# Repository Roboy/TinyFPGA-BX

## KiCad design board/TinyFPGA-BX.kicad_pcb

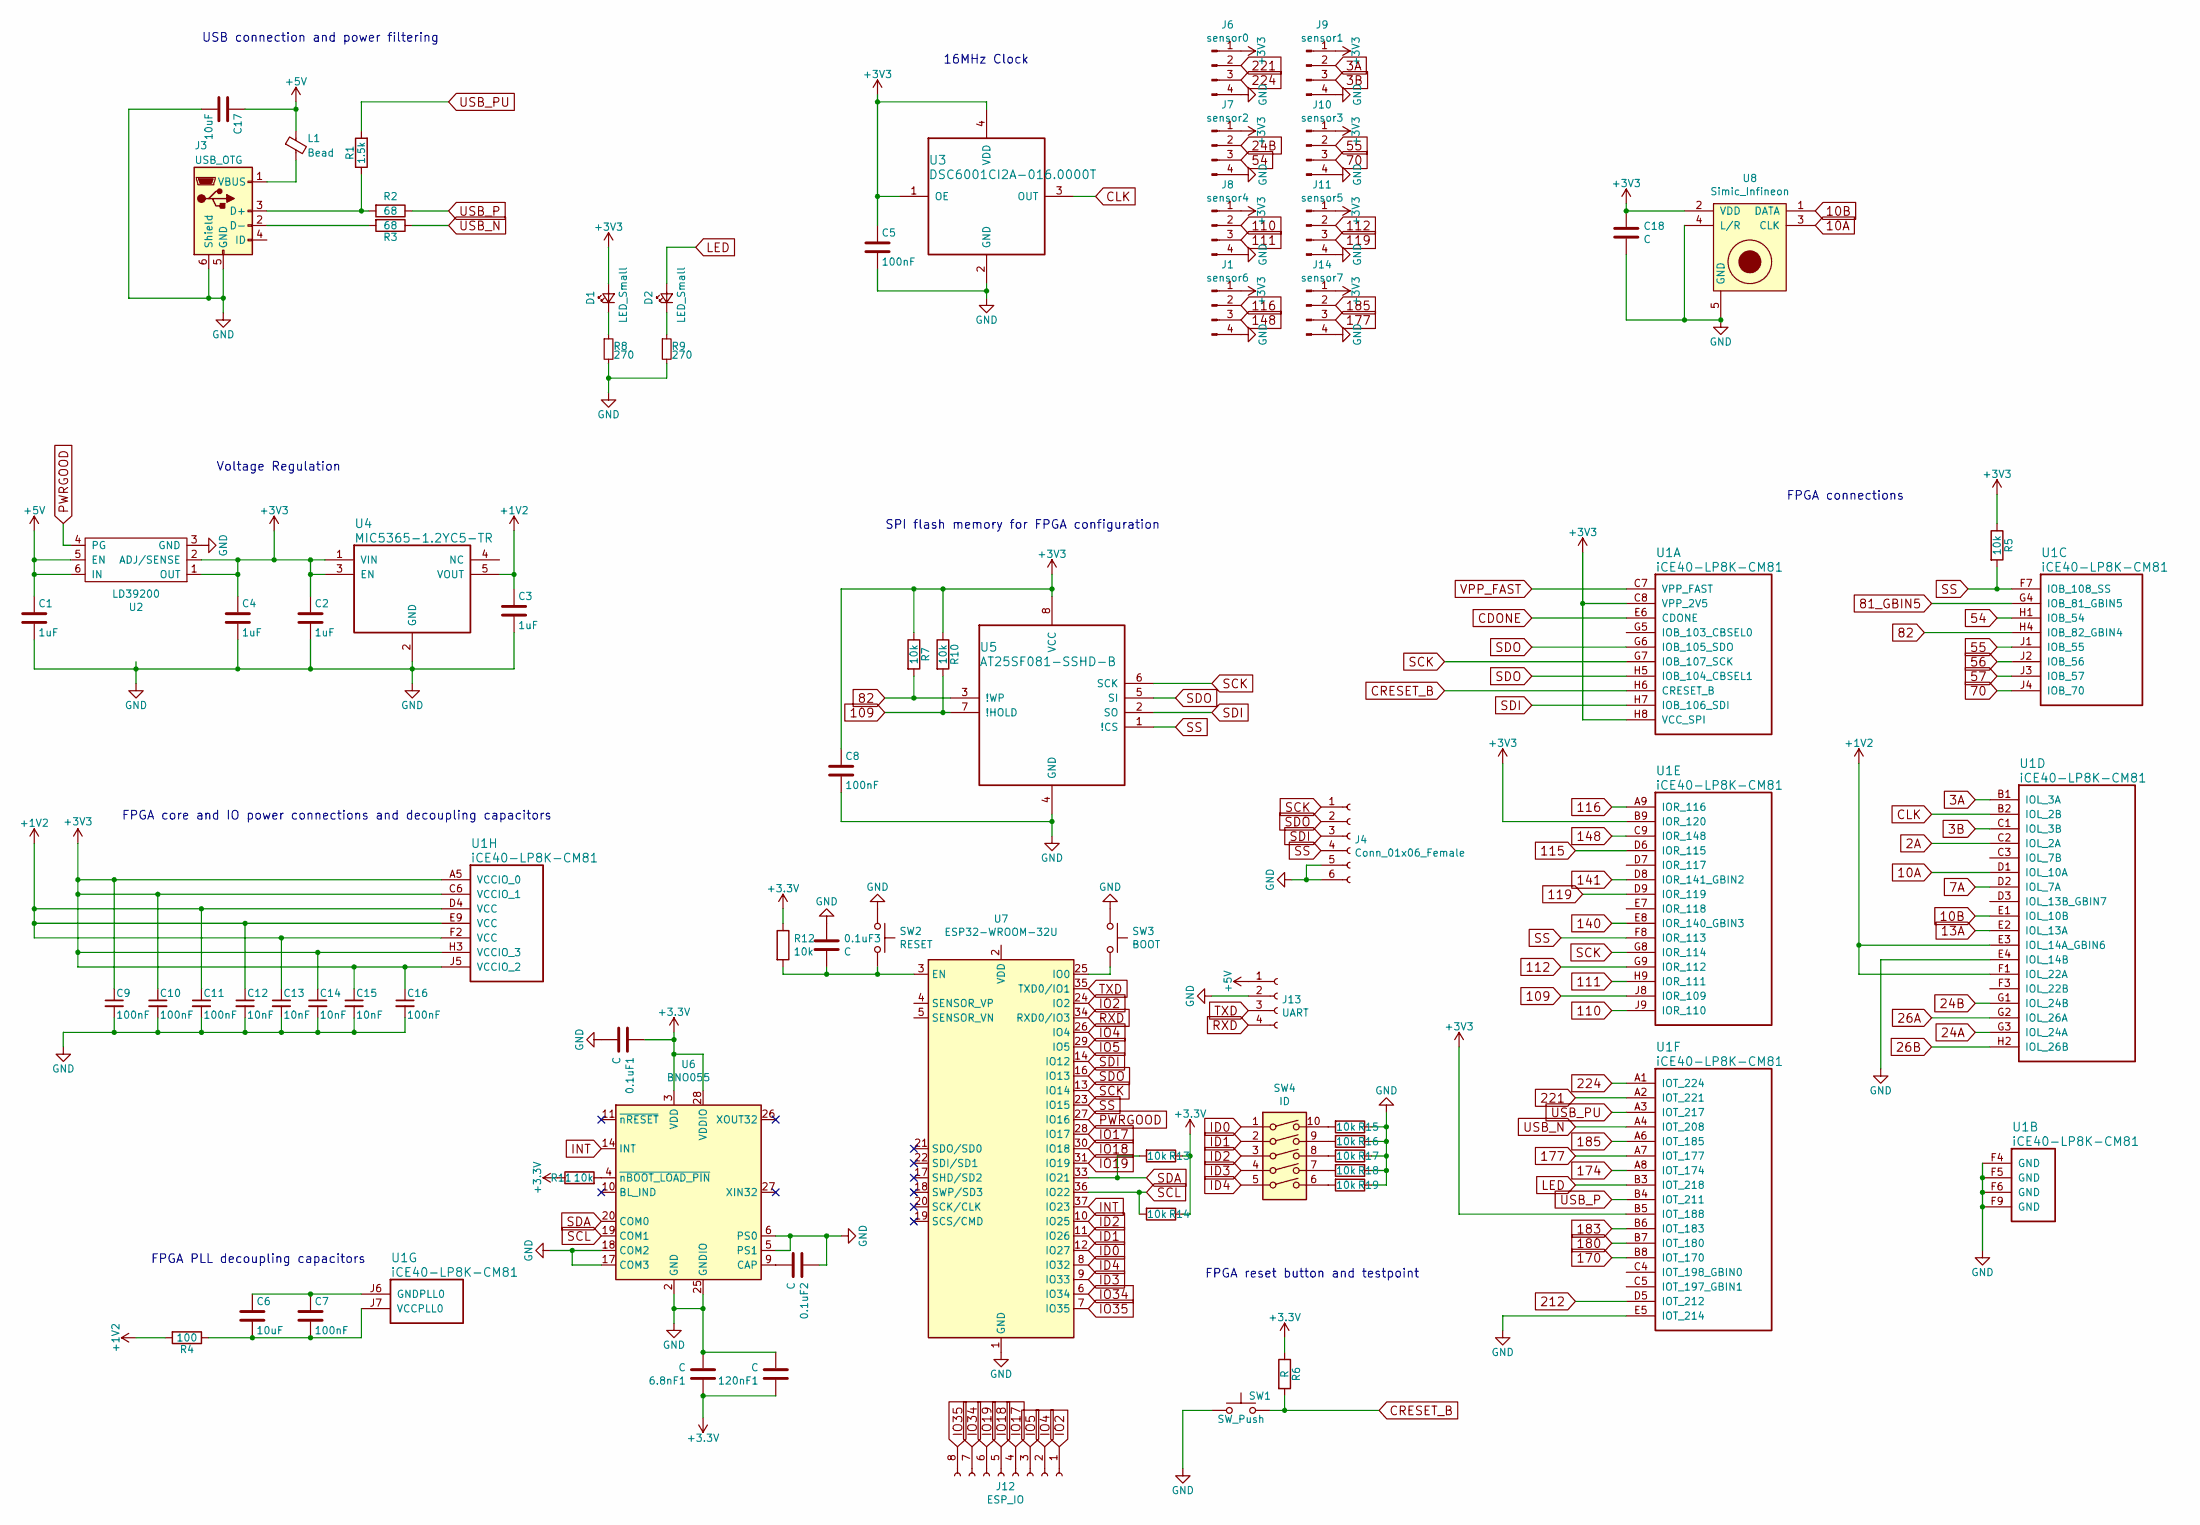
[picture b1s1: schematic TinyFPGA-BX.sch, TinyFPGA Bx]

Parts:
0.1uF1, 0.1uF2, 0.1uF3, 6.8nF1, 120nF1: C; C_0402_1005Metric
C1, C2, C3, C4: 1uF; C_0402_NoSilk
C5, C7, C8, C9, C10, C11, C16: 100nF; C_0402_NoSilk
C6, C17: 10uF; C_0603
C12, C13, C14, C15: 10nF; C_0402_NoSilk
C18: C; C_01005_0402Metric
D1, D2: LED_Small; LED_0603
J1: sensor6; TE-Connectivity_Micro-Match_connector_02x02_Pitch_1.27mm
J3: USB_OTG; USB_Micro-B_Molex_47346-0001
J4: Conn_01x06_Female; TE-Connectivity_Micro-Match_connector_02x03_Pitch_1.27mm
J6: sensor0; TE-Connectivity_Micro-Match_connector_02x02_Pitch_1.27mm
J7: sensor2; TE-Connectivity_Micro-Match_connector_02x02_Pitch_1.27mm
J8: sensor4; TE-Connectivity_Micro-Match_connector_02x02_Pitch_1.27mm
J9: sensor1; TE-Connectivity_Micro-Match_connector_02x02_Pitch_1.27mm
J10: sensor3; TE-Connectivity_Micro-Match_connector_02x02_Pitch_1.27mm
J11: sensor5; TE-Connectivity_Micro-Match_connector_02x02_Pitch_1.27mm
J12: ESP_IO; PinHeader_1x08_P2.54mm_Vertical
J13: UART; PinHeader_1x04_P2.54mm_Vertical
J14: sensor7; TE-Connectivity_Micro-Match_connector_02x02_Pitch_1.27mm
L1: Bead; L_0603
R1: 1.5k; R_0402_NoSilk
R2, R3: 68; R_0402_NoSilk
R4: 100; R_0402_NoSilk
R5, R7, R10: 10k; R_0402_NoSilk
R6: R; R_0402
R8, R9: 270; R_0402_NoSilk
R11, R12, R13, R14, R15, R16, R17, R18, R19: 10k; R_0402_1005Metric
SW1: SW_Push; PTS_810_SMT_Switch
SW2: RESET; SW_SPST_KXT3
SW3: BOOT; SW_SPST_KXT3
SW4: ID; SW_DIP_SPSTx05_Slide_6.7x14.26mm_W6.73mm_P2.54mm_LowProfile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
U1: iCE40-LP8K-CM81; CM81
U2: LD39200; DFN-6-1EP_3x3mm_P0.95mm_EP1.7x2.6mm
U3: DSC6001CI2A-016.0000T; CDFN3225-4LD-PL-1
U4: MIC5365-1.2YC5-TR; SC-70-C5
U5: AT25SF081-SSHD-B; SOIC-8_3.9x4.9mm_P1.27mm
U6: BNO055; LGA-28_5.2x3.8mm_P0.5mm
U7: ESP32-WROOM-32U
U8: Simic_Infineon; IM69D130_Simic_uPhone

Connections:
2A: U1.C2 (IOL_2A)
3A: J9.2, U1.B1 (IOL_3A)
3B: J9.3, U1.C1 (IOL_3B)
7A: U1.D2 (IOL_7A)
10A: U1.D1 (IOL_10A), U8.3 (CLK)
10B: U1.E1 (IOL_10B), U8.1 (DATA)
13A: U1.E2 (IOL_13A)
24A: U1.G3 (IOL_24A)
24B: J7.2, U1.G1 (IOL_24B)
26A: U1.G2 (IOL_26A)
26B: U1.H2 (IOL_26B)
54: J7.3, U1.H1 (IOB_54)
55: J10.2, U1.J1 (IOB_55)
56: U1.J2 (IOB_56)
57: U1.J3 (IOB_57)
70: J10.3, U1.J4 (IOB_70)
81_GBIN5: U1.G4 (IOB_81_GBIN5)
82: R7.2, U1.H4 (IOB_82_GBIN4), U5.3 (!WP)
109: R10.2, U1.J8 (IOR_109), U5.7 (!HOLD)
110: J8.2, U1.J9 (IOR_110)
111: J8.3, U1.H9 (IOR_111)
112: J11.2, U1.G9 (IOR_112)
115: U1.D6 (IOR_115)
116: J1.2, U1.A9 (IOR_116)
119: J11.3, U1.D9 (IOR_119)
140: U1.E8 (IOR_140_GBIN3)
141: U1.D8 (IOR_141_GBIN2)
148: J1.3, U1.C9 (IOR_148)
170: U1.B8 (IOT_170)
174: U1.A8 (IOT_174)
177: J14.3, U1.A7 (IOT_177)
180: U1.B7 (IOT_180)
183: U1.B6 (IOT_183)
185: J14.2, U1.A6 (IOT_185)
212: U1.D5 (IOT_212)
221: J6.2, U1.A2 (IOT_221)
224: J6.3, U1.A1 (IOT_224)
+1V2: C3.1, C11.1, C12.1, C13.1, R4.2, U1.D4 (VCC), U1.E3 (IOL_14A_GBIN6), U1.E9 (VCC), U1.F1 (IOL_22A), U1.F2 (VCC), U4.5 (VOUT)
+5V: C1.1, C17.1, J13.1, L1.1, U2.5 (EN), U2.6 (IN)
CDONE: U1.E6 (CDONE)
CLK: U1.B2 (IOL_2B), U3.3 (OUT)
CRESET_B: R6.2, SW1.2, U1.H6 (CRESET_B)
GND: 0.1uF1.2, 0.1uF2.1, 0.1uF3.1, 6.8nF1.2, 120nF1.2, C1.2, C2.2, C3.2, C4.2, C5.2, C8.2, C9.2, C10.2, C11.2, C12.2, C13.2, C14.2, C15.2, C16.2, C17.2, C18.2, J1.4, J3.5 (GND), J3.6 (Shield), J4.5, J4.6, J6.4, J7.4, J8.4, J9.4, J10.4, J11.4, J13.2, J14.4, R8.2, R9.2, R15.1, R16.1, R17.1, R18.1, R19.1, SW1.1, SW2.1, SW3.1, U1.E4 (IOL_14B), U1.E5 (IOT_214), U1.F4 (GND), U1.F5 (GND), U1.F6 (GND), U1.F9 (GND), U2.3 (GND), U3.2 (GND), U4.2 (GND), U5.4 (GND), U6.2 (GND), U6.5 (PS1), U6.6 (PS0), U6.15 (GNDIO), U6.16 (GNDIO), U6.17 (COM3), U6.18 (COM2), U6.25 (GNDIO), U7.1 (GND), U7.15 (GND), U7.38 (GND), U8.4 (L/R), U8.5 (GND)
ID0: SW4.1, U7.12 (IO27)
ID1: SW4.2, U7.11 (IO26)
ID2: SW4.3, U7.10 (IO25)
ID3: SW4.4, U7.9 (IO33)
ID4: SW4.5, U7.8 (IO32)
INT: U6.14 (INT), U7.37 (IO23)
IO2: J12.1, U7.24 (IO2)
IO4: J12.2, U7.26 (IO4)
IO5: J12.3, U7.29 (IO5)
IO17: J12.4, U7.28 (IO17)
IO18: J12.5, U7.30 (IO18)
IO19: J12.6, U7.31 (IO19)
IO34: J12.7, U7.6 (IO34)
IO35: J12.8, U7.7 (IO35)
LED: D2.2 (A), U1.B3 (IOT_218)
unnamed: 0.1uF2.2, U6.9 (CAP)
unnamed: 0.1uF3.2, R12.2, SW2.2, U7.3 (EN)
unnamed: C6.1, C7.1, U1.J6 (GNDPLL0)
unnamed: C6.2, C7.2, R4.1, U1.J7 (VCCPLL0)
unnamed: D1.1 (K), R8.1
unnamed: D2.1 (K), R9.1
unnamed: J3.1 (VBUS), L1.2
unnamed: J3.2 (D-), R3.2
unnamed: J3.3 (D+), R1.1, R2.2
unnamed: R11.2, U6.4 (~nBOOT_LOAD_PIN)
unnamed: R15.2, SW4.10
unnamed: R16.2, SW4.9
unnamed: R17.2, SW4.8
unnamed: R18.2, SW4.7
unnamed: R19.2, SW4.6
unnamed: SW3.2, U7.25 (IO0)
PWRGOOD: U2.4 (PG), U7.27 (IO16)
RXD: J13.4, U7.34 (RXD0/IO3)
SCK: J4.1, U1.G7 (IOB_107_SCK), U1.G8 (IOR_114), U5.6 (SCK), U7.13 (IO14)
SCL: R14.2, U6.19 (COM1), U7.36 (IO22)
SDA: R13.2, U6.20 (COM0), U7.33 (IO21)
SDI: J4.3, U1.H7 (IOB_106_SDI), U5.2 (SO), U7.14 (IO12)
SDO: J4.2, U1.G6 (IOB_105_SDO), U1.H5 (IOB_104_CBSEL1), U5.5 (SI), U7.16 (IO13)
SS: J4.4, R5.2, U1.F7 (IOB_108_SS), U1.F8 (IOR_113), U5.1 (!CS), U7.23 (IO15)
TXD: J13.3, U7.35 (TXD0/IO1)
USB_N: R3.1, U1.A4 (IOT_208)
USB_P: R2.1, U1.B4 (IOT_211)
USB_PU: R1.2, U1.A3 (IOT_217)
VPP_FAST: U1.C7 (VPP_FAST)

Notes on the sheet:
FPGA core and IO power connections and decoupling capacitors
FPGA PLL decoupling capacitors
USB connection and power filtering
Voltage Regulation
16MHz Clock
SPI flash memory for FPGA configuration
FPGA reset button and testpoint
FPGA connections

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
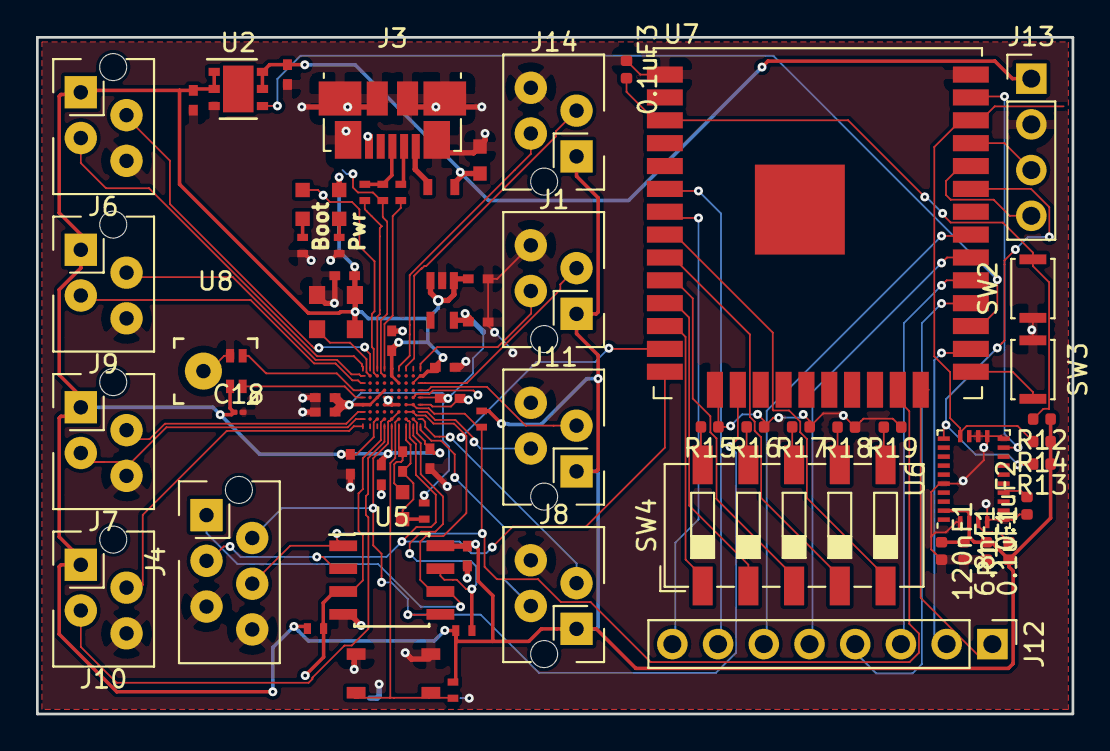
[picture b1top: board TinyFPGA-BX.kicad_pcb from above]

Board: 2 copper layers, 57.5 x 37.6 mm, 69 parts (0 on the bottom side), 69 nets.

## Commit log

2019-05-28 extended for lighthouse sensors
2019-06-01 added esp32 and imu, reduced to 2 layer board, layout only drafted
2019-06-04 cutting se woods
2019-06-06 better
2019-06-09 layout done
2019-06-09 aisler ordre
2019-06-29 with darkroom ts4231 compiling and seems to work
2019-07-29 with solder mask
